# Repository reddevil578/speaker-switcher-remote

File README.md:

# speaker-switcher-remote
12V remote controlled audio component trigger as KiCAD project

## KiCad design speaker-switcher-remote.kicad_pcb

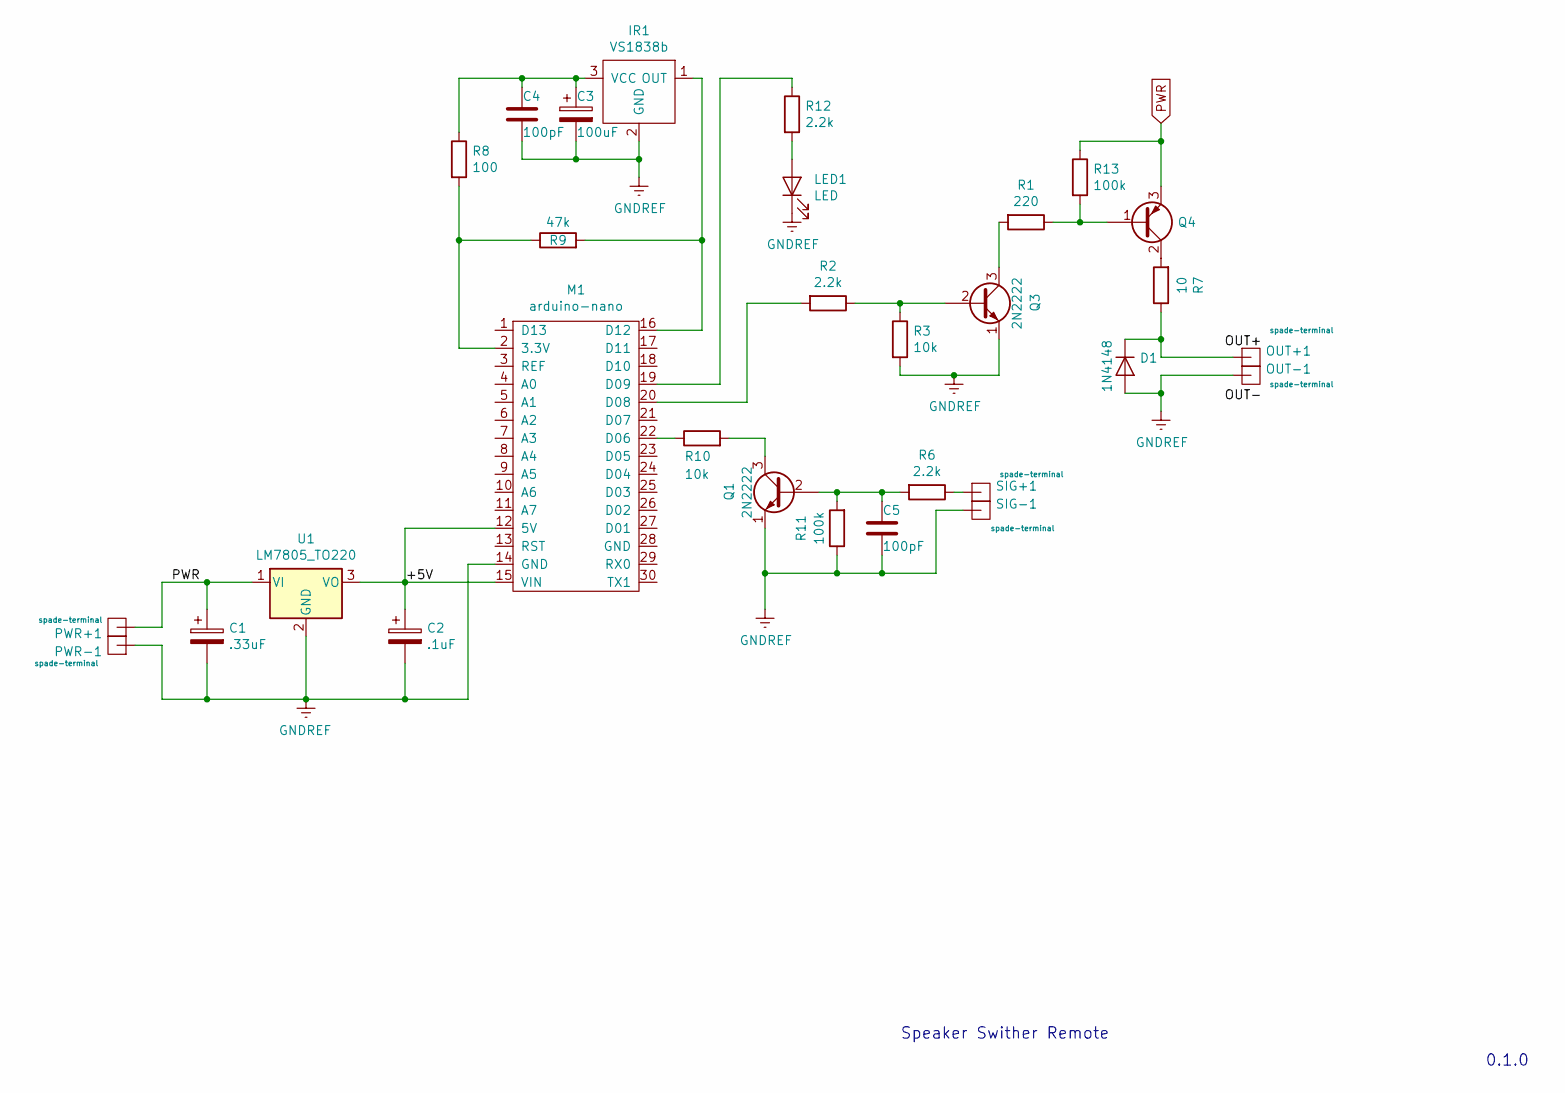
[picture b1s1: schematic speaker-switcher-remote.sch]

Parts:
C1: .33uF; C_Disc_D5.0mm_W2.5mm_P5.00mm
C2: .1uF; C_Disc_D6.0mm_W2.5mm_P5.00mm
C3: 100uF; CP_Radial_D10.0mm_P2.50mm
C4, C5: 100pF; C_Disc_D6.0mm_W2.5mm_P5.00mm
D1: 1N4148; D_DO-41_SOD81_P7.62mm_Horizontal
IR1: VS1838b; PinHeader_1x03_P2.54mm_Vertical
LED1: LED; JST_XH_B2B-XH-A_1x02_P2.50mm_Vertical
M1: arduino-nano
OUT+1: spade-terminal; SpadeTerminal635
OUT-1: spade-terminal; SpadeTerminal635
PWR+1: spade-terminal; SpadeTerminal635
PWR-1: spade-terminal; SpadeTerminal635
Q1, Q3: 2N2222; TO-92
Q4: Q_PNP_BCE; TO-220-3_Vertical
R1: 220; R_Axial_DIN0207_L6.3mm_D2.5mm_P7.62mm_Horizontal
R2, R6, R12: 2.2k; R_Axial_DIN0207_L6.3mm_D2.5mm_P7.62mm_Horizontal
R3, R10: 10k; R_Axial_DIN0207_L6.3mm_D2.5mm_P7.62mm_Horizontal
R7: 10; R_Axial_DIN0516_L15.5mm_D5.0mm_P20.32mm_Horizontal
R8: 100; R_Axial_DIN0207_L6.3mm_D2.5mm_P7.62mm_Horizontal
R9: 47k; R_Axial_DIN0207_L6.3mm_D2.5mm_P7.62mm_Horizontal
R11, R13: 100k; R_Axial_DIN0207_L6.3mm_D2.5mm_P7.62mm_Horizontal
SIG+1: spade-terminal; SpadeTerminal635
SIG-1: spade-terminal; SpadeTerminal635
U1: LM7805_TO220; TO-220-3_Vertical

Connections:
/+5V: C2.1, M1.12 (5V), M1.15 (VIN), U1.3 (VO)
GNDREF: C1.2, C2.2, C3.2, C4.2, C5.2, D1.2 (A), IR1.2 (GND), LED1.1 (K), M1.14 (GND), OUT-1.1, PWR-1.1, Q1.1 (E), Q3.1 (E), R3.2, R11.1, SIG-1.1, U1.2 (GND)
unnamed: C3.1, C4.1, IR1.3 (VCC), R8.1
unnamed: C5.1, Q1.2 (B), R6.2, R11.2
unnamed: D1.1 (K), OUT+1.1, R7.1
unnamed: IR1.1 (OUT), M1.16 (D12), R9.2
unnamed: LED1.2 (A), R12.2
unnamed: M1.2 (3.3V), R8.2, R9.1
unnamed: M1.19 (D09), R12.1
unnamed: M1.20 (D08), R2.2
unnamed: M1.22 (D06), R10.1
unnamed: Q1.3 (C), R10.2
unnamed: Q3.2 (B), R2.1, R3.1
unnamed: Q3.3 (C), R1.2
unnamed: Q4.1 (B), R1.1, R13.2
unnamed: Q4.2 (C), R7.2
unnamed: R6.1, SIG+1.1
PWR: C1.1, PWR+1.1, Q4.3 (E), R13.1, U1.1 (VI)

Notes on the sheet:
Speaker Swither Remote
0.1.0

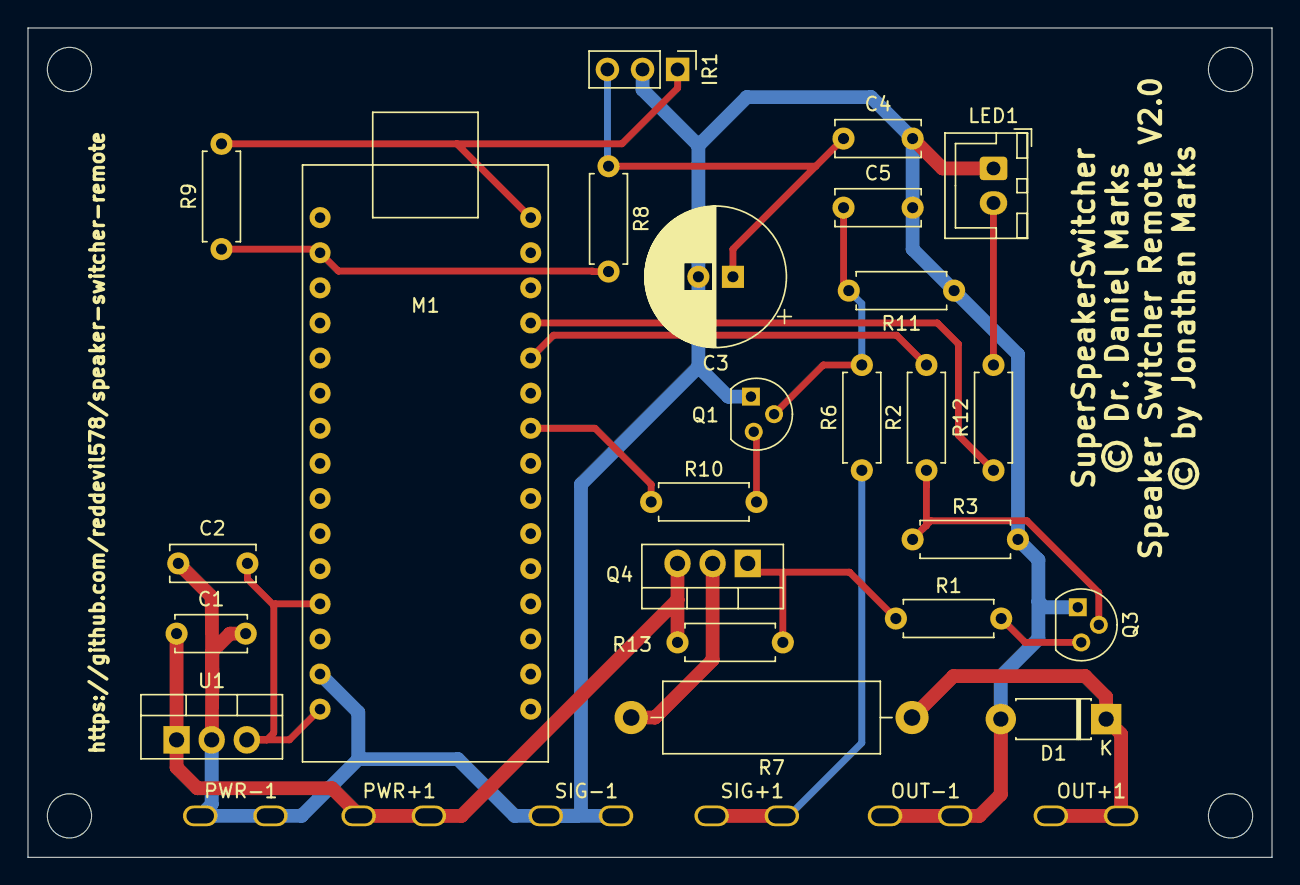
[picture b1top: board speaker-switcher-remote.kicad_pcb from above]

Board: 2 copper layers, 90.0 x 60.0 mm, 30 parts (0 on the bottom side), 18 nets.

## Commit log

2021-01-23 Initial design
2021-01-23 Updated with arduino src code
2021-01-23 Moved items
2021-01-23 Commented, cleanup up, and moved arduino sketch
2021-01-23 Commentary and simplified IrCommand
2021-01-25 Moved labels
2021-01-29 Add rescure files
2021-01-30 Updated as per Dan's recommendations
2021-01-30 Reworking pcb
2021-01-30 Updated board
2021-01-30 New PCB layout
2021-01-30 Stabilize signal input
2021-01-31 Updated PCB but not plots
2021-01-31 Updated plots
2021-01-31 Elongated board to required mounting width
2021-01-31 Updated PDFs
2021-02-01 Updated board as per Dan's remarks
2021-02-13 Added indicator LED to d09
2021-02-14 Update for latest circuit changes
2021-03-07 Updated w/PNP output stage
2021-03-07 Rev 2.0
2021-03-07 Fixed trace width

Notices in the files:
speaker-switcher-remote.kicad_pcb:
© Dr. Daniel Marks
© by Jonathan Marks
